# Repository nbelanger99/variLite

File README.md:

# variLite

The variLite is a minimalistic, open-source variometer design for freeflight and powered flight use cases such as paragliding, paramotoring, hanglinding etc. 

The design is yet to be manufactured, programmed, and tested. If working firmware is developed, it will be open-sourced as well and linked here

<br>

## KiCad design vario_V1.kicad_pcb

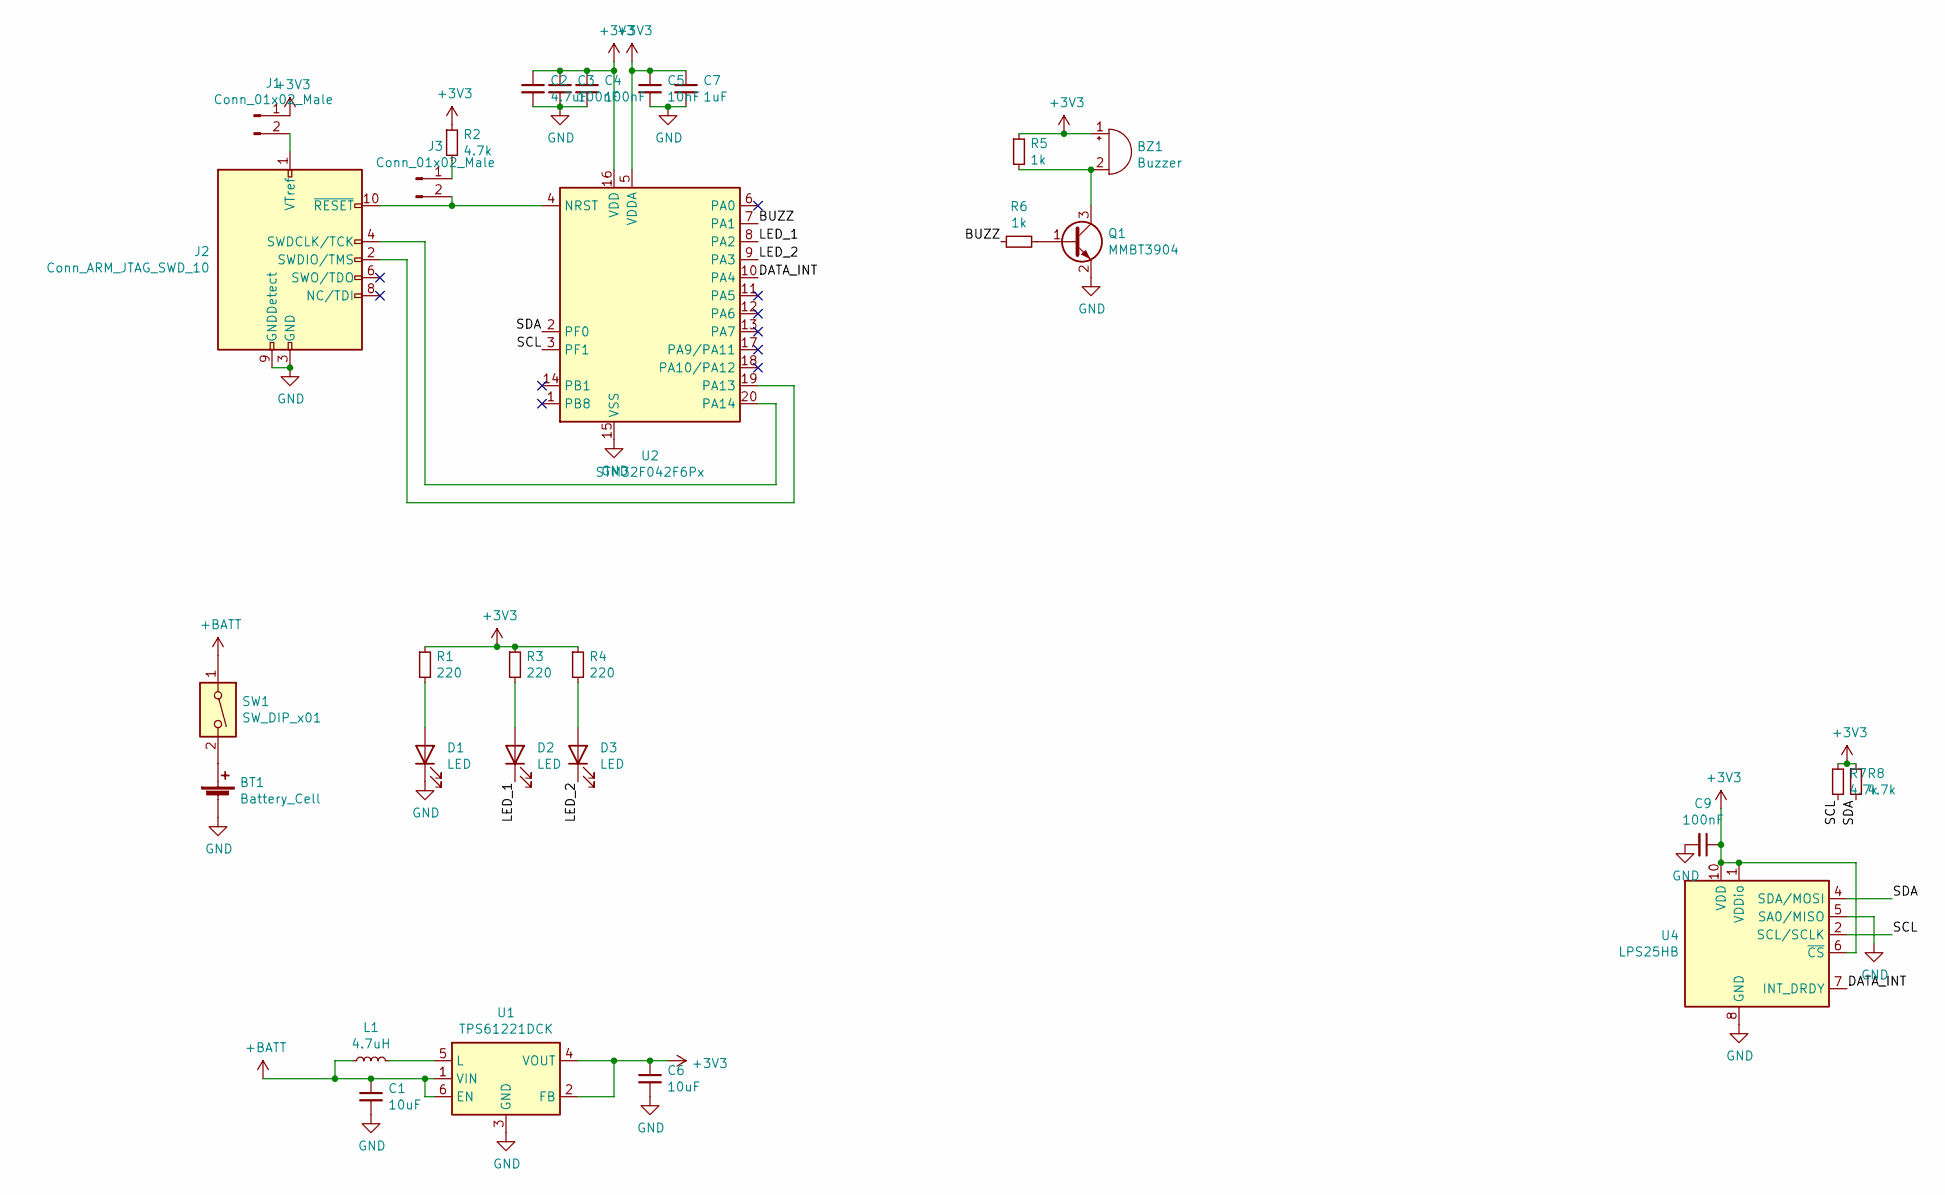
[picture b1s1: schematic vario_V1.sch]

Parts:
BT1: Battery_Cell; BatteryHolder_Keystone_2466_1xAAA
BZ1: Buzzer; Buzzer_TDK_PS1240P02BT_D12.2mm_H6.5mm
C1, C6: 10uF; C_0603_1608Metric_Pad1.05x0.95mm_HandSolder
C2: 4.7uF; C_0603_1608Metric_Pad1.05x0.95mm_HandSolder
C3, C4, C9: 100nF; C_0402_1005Metric
C5: 10nF; C_0402_1005Metric
C7: 1uF; C_0603_1608Metric_Pad1.05x0.95mm_HandSolder
D1, D2, D3: LED; LED_1206_3216Metric_Castellated
J1, J3: Conn_01x02_Male; PinHeader_1x02_P2.54mm_Vertical
J2: Conn_ARM_JTAG_SWD_10; PinHeader_2x05_P1.27mm_Vertical
L1: 4.7uH; L_Wuerth_WE-TPC-3816
Q1: MMBT3904; SOT-23
R1, R3, R4: 220; R_0603_1608Metric_Pad1.05x0.95mm_HandSolder
R2, R7, R8: 4.7k; R_0603_1608Metric_Pad1.05x0.95mm_HandSolder
R5, R6: 1k; R_0603_1608Metric_Pad1.05x0.95mm_HandSolder
SW1: SW_DIP_x01; PinHeader_1x02_P2.54mm_Vertical
U1: TPS61221DCK; Texas_R-PDSO-G6
U2: STM32F042F6Px; TSSOP-20_4.4x6.5mm_P0.65mm
U4: LPS25HB; ST_HLGA-10_2.5x2.5mm_P0.6mm_LayoutBorder3x2y

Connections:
+3V3: BZ1.1 (-), C2.1, C3.1, C4.1, C5.1, C6.1, C7.1, C9.1, J1.1, R1.1, R2.1, R3.1, R4.1, R5.1, R7.2, R8.1, U1.2 (FB), U1.4 (VOUT), U2.5 (VDDA), U2.16 (VDD), U4.1 (VDDio), U4.6 (~CS), U4.10 (VDD)
+BATT: C1.1, L1.1, SW1.1, U1.1 (VIN), U1.6 (EN)
/BUZZ: R6.1, U2.7 (PA1)
/DATA_INT: U2.10 (PA4), U4.7 (INT_DRDY)
/LED_1: D2.1 (K), U2.8 (PA2)
/LED_2: D3.1 (K), U2.9 (PA3)
/SCL: R7.1, U2.3 (PF1), U4.2 (SCL/SCLK)
/SDA: R8.2, U2.2 (PF0), U4.4 (SDA/MOSI)
GND: BT1.2 (-), C1.2, C2.2, C3.2, C4.2, C5.2, C6.2, C7.2, C9.2, D1.1 (K), J2.3 (GND), J2.5 (GND), J2.9 (GNDDetect), Q1.2 (E), U1.3 (GND), U2.15 (VSS), U4.3 (GND), U4.5 (SA0/MISO), U4.8 (GND), U4.9 (GND)
unnamed: BT1.1 (+), SW1.2
unnamed: BZ1.2 (+), Q1.3 (C), R5.2
unnamed: D1.2 (A), R1.2
unnamed: D2.2 (A), R3.2
unnamed: D3.2 (A), R4.2
unnamed: J1.2, J2.1 (VTref)
unnamed: J2.2 (SWDIO/TMS), U2.19 (PA13)
unnamed: J2.4 (SWDCLK/TCK), U2.20 (PA14)
unnamed: J2.10 (~RESET~), J3.2, U2.4 (NRST)
unnamed: J3.1, R2.2
unnamed: L1.2, U1.5 (L)
unnamed: Q1.1 (B), R6.2

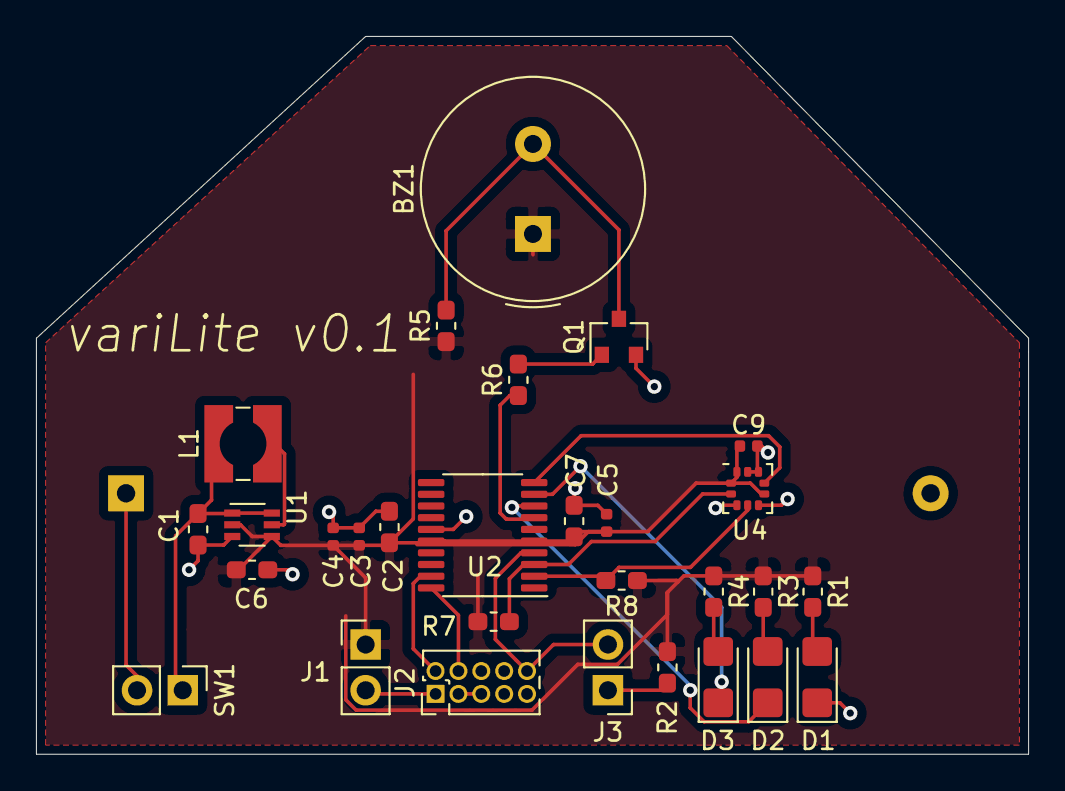
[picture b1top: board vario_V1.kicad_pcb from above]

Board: 2 copper layers, 55.1 x 39.9 mm, 30 parts (1 on the bottom side), 21 nets.

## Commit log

2020-11-18 Starting initial routing
2020-11-18 Removing LCD
2020-11-18 Basic layout done- passes DRC, not dense, no power plane
2020-11-18 Added power plane
2020-11-18 Silkscreen: fixed designator, added text
2021-02-10 Finishing layout
2021-02-10 Removing cache file, adding gitignore
2021-02-13 Adding media & readme
